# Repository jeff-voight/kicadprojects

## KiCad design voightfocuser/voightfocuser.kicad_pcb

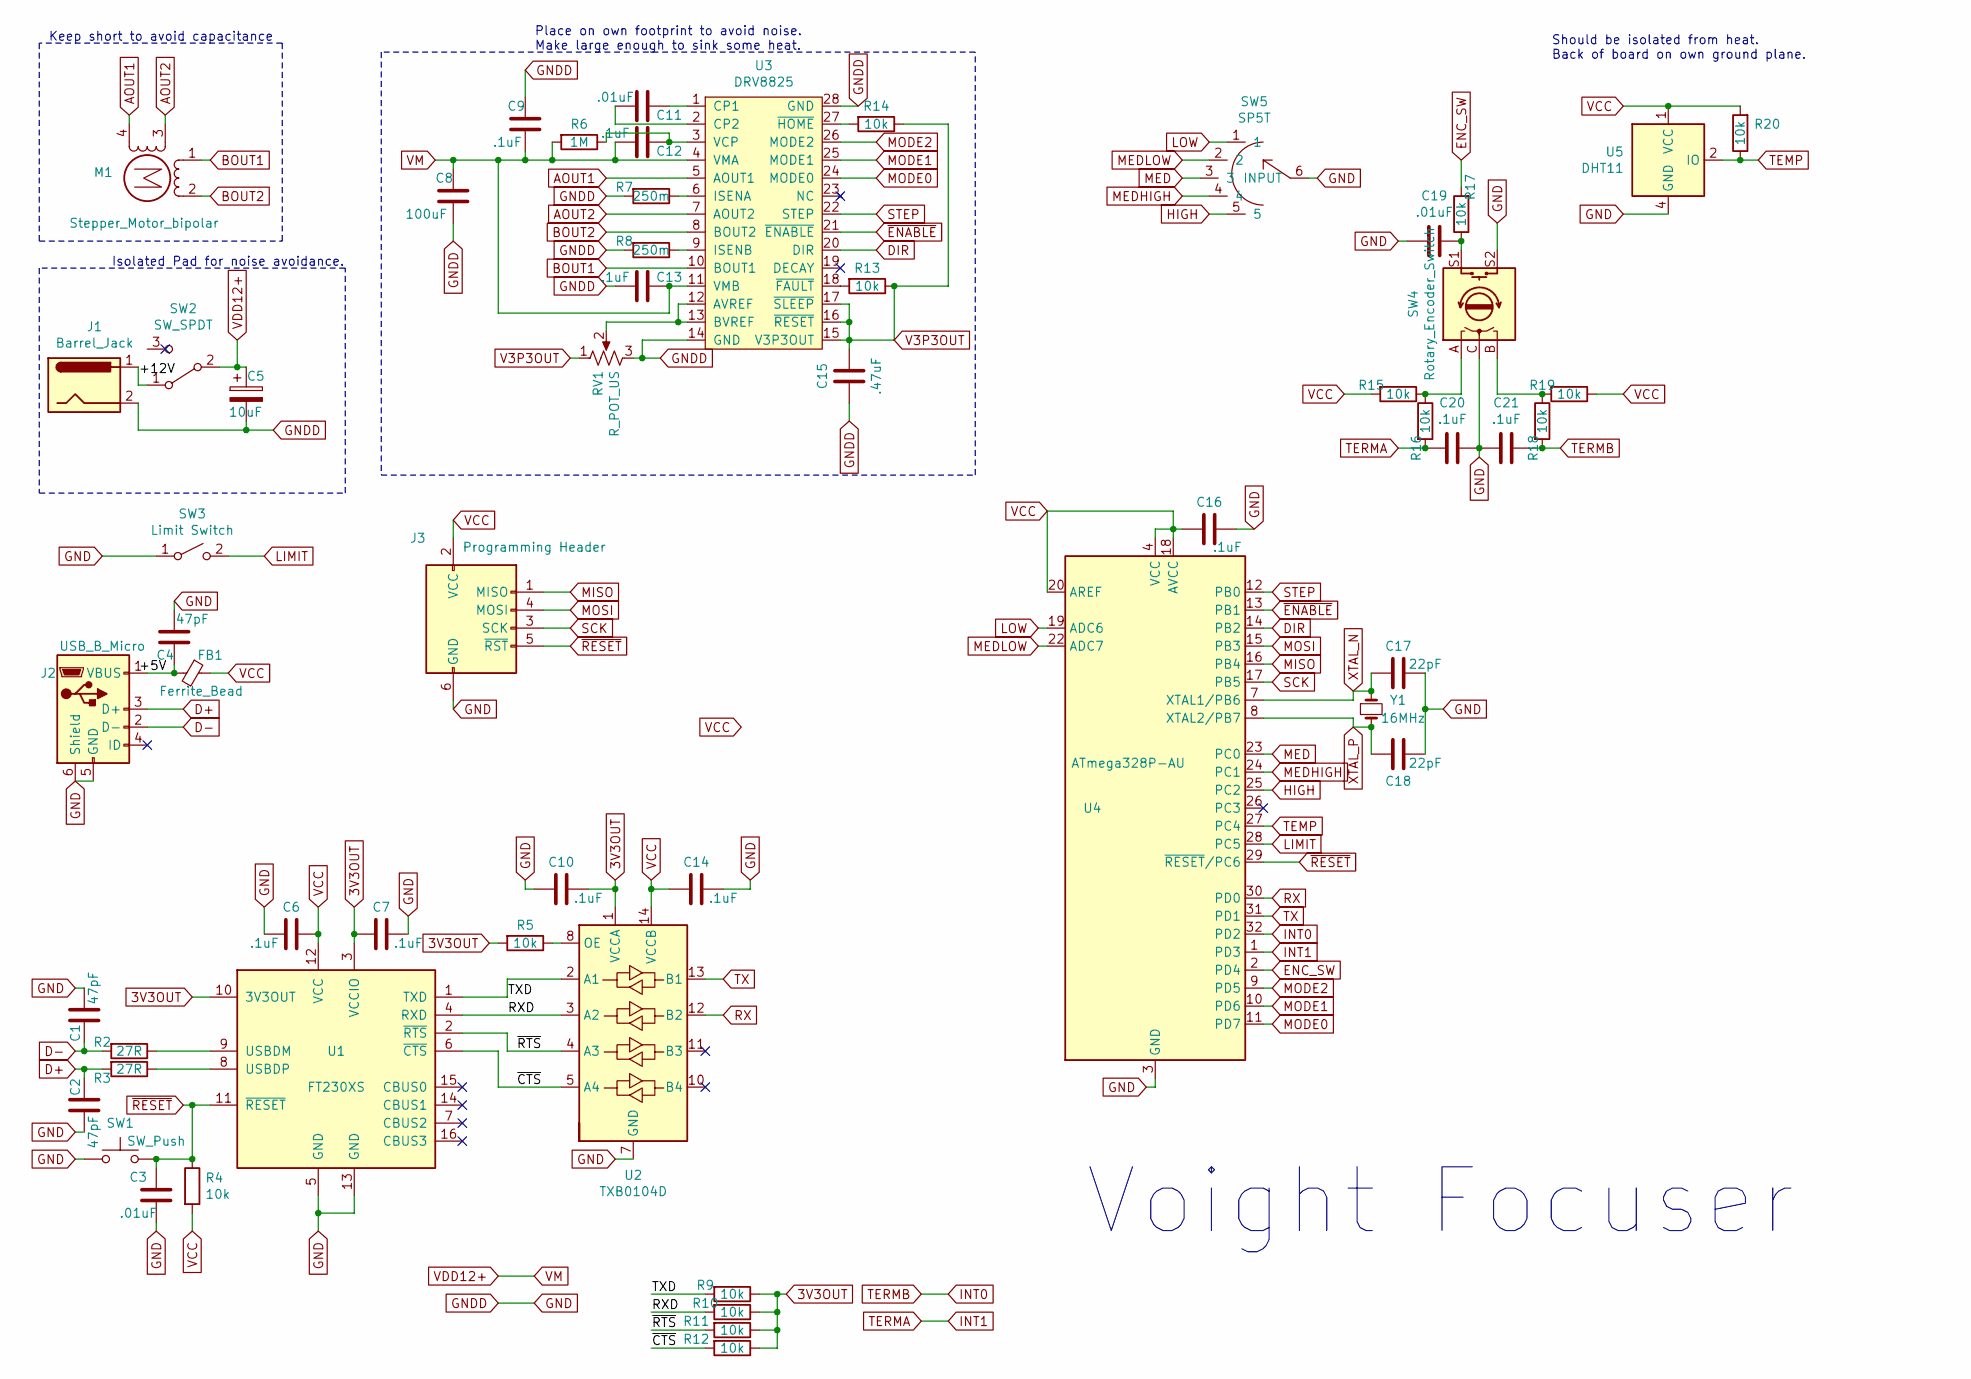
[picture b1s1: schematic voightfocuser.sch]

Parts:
C1, C2, C4: 47pF; C_0805_2012Metric_Pad1.15x1.40mm_HandSolder
C3, C11, C19: .01uF; C_0805_2012Metric_Pad1.15x1.40mm_HandSolder
C5: 10uF; C_0805_2012Metric_Pad1.15x1.40mm_HandSolder
C6, C7, C9, C10, C12, C13, C14, C16, C20, C21: .1uF; C_0805_2012Metric_Pad1.15x1.40mm_HandSolder
C8: 100uF; C_0805_2012Metric_Pad1.15x1.40mm_HandSolder
C15: .47uF; C_0805_2012Metric_Pad1.15x1.40mm_HandSolder
C17, C18: 22pF; C_0805_2012Metric_Pad1.15x1.40mm_HandSolder
FB1: Ferrite_Bead; LairdTech_28C0236-0JW-10
J1: Barrel_Jack; BarrelJack_CUI_PJ-063AH_Horizontal
J2: USB_B_Micro; USB_Micro-B_Amphenol_10103594-0001LF_Horizontal
J3: Programming Header; PinHeader_1x06_P2.54mm_Vertical
M1: Stepper_Motor_bipolar; PinHeader_1x04_P2.54mm_Vertical
R2, R3: 27R; R_0805_2012Metric_Pad1.15x1.40mm_HandSolder
R4, R5, R9, R10, R11, R12, R13, R14, R15, R16, R17, R18, R19, R20: 10k; R_0805_2012Metric_Pad1.15x1.40mm_HandSolder
R6: 1M; R_0805_2012Metric_Pad1.15x1.40mm_HandSolder
R7, R8: 250m; R_0805_2012Metric_Pad1.15x1.40mm_HandSolder
RV1: R_POT_US; Potentiometer_Bourns_TC33X_Vertical
SW1: SW_Push; PinHeader_1x02_P2.54mm_Vertical
SW2: SW_SPDT; SW_Slide_1P2T_CK_OS102011MS2Q
SW3: Limit Switch; PinHeader_1x02_P2.54mm_Vertical
SW4: Rotary_Encoder_Switch; RotaryEncoder_Alps_EC12E-Switch_Vertical_H20mm
SW5: SP5T; PinHeader_1x06_P2.54mm_Vertical
U1: FT230XS; SSOP-16_3.9x4.9mm_P0.635mm
U2: TXB0104D; SOIC-14_3.9x8.7mm_P1.27mm
U3: DRV8825; HTSSOP-28-1EP_4.4x9.7mm_P0.65mm_EP3.4x9.5mm_Mask2.4x6.17mm_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
U4: ATmega328P-AU; TQFP-32_7x7mm_P0.8mm
U5: DHT11; Aosong_DHT11_5.5x12.0_P2.54mm
Y1: 16MHz; Crystal_SMD_HC49-SD

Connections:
3V3OUT: C7.2, C10.1, R5.2, R9.1, R10.1, R11.1, R12.1, U1.3 (VCCIO), U1.10 (3V3OUT), U2.1 (VCCA)
/+12V: J1.1, SW2.1 (A)
/RXD: R10.2, U1.4 (RXD), U2.3 (A2)
/TXD: R9.2, U1.1 (TXD), U2.2 (A1)
/~CTS: R12.2, U1.6 (~CTS), U2.5 (A4)
/~RTS: R11.2, U1.2 (~RTS), U2.4 (A3)
AOUT1: M1.4, U3.5 (AOUT1)
AOUT2: M1.3, U3.7 (AOUT2)
BOUT1: M1.1, U3.10 (BOUT1)
BOUT2: M1.2 (-), U3.8 (BOUT2)
D+: C2.1, J2.3 (D+), R3.2
D-: C1.2, J2.2 (D-), R2.2
DIR: U3.20 (DIR), U4.14 (PB2)
ENC_SW: R17.2, U4.2 (PD4)
GND: C1.1, C2.2, C3.1, C4.1, C5.2, C6.2, C7.1, C8.2, C9.1, C10.2, C13.2, C14.1, C15.2, C16.1, C17.1, C18.1, C19.2, C20.1, C21.2, J1.2, J2.5 (GND), J2.6 (Shield), J3.6 (GND), R7.2, R8.2, RV1.3, SW1.1, SW3.1 (A), SW4.C, SW4.S2, SW5.6 (INPUT), U1.5 (GND), U1.13 (GND), U2.7 (GND), U3.14 (GND), U3.28 (GND), U4.3 (GND), U4.5 (GND), U4.21 (GND), U5.4 (GND)
HIGH: SW5.5, U4.25 (PC2)
INT0: C21.1, R18.2, U4.32 (PD2)
INT1: C20.2, R16.2, U4.1 (PD3)
LIMIT: SW3.2 (B), U4.28 (PC5)
LOW: SW5.1, U4.19 (ADC6)
MED: SW5.3, U4.23 (PC0)
MEDHIGH: SW5.4, U4.24 (PC1)
MEDLOW: SW5.2, U4.22 (ADC7)
MISO: J3.1 (MISO), U4.16 (PB4)
MODE0: U3.24 (MODE0), U4.11 (PD7)
MODE1: U3.25 (MODE1), U4.10 (PD6)
MODE2: U3.26 (MODE2), U4.9 (PD5)
MOSI: J3.4 (MOSI), U4.15 (PB3)
unnamed: C4.2, FB1.2, J2.1 (VBUS)
unnamed: C11.1, U3.1 (CP1)
unnamed: C11.2, U3.2 (CP2)
unnamed: C12.1, R6.1, U3.3 (VCP)
unnamed: C19.1, R17.1, SW4.S1
unnamed: R2.1, U1.9 (USBDM)
unnamed: R3.1, U1.8 (USBDP)
unnamed: R5.1, U2.8 (OE)
unnamed: R7.1, U3.6 (ISENA)
unnamed: R8.1, U3.9 (ISENB)
unnamed: R13.2, U3.18 (~FAULT)
unnamed: R14.2, U3.27 (~HOME)
unnamed: R15.1, R16.1, SW4.A
unnamed: R18.1, R19.2, SW4.B
unnamed: RV1.2, U3.12 (AVREF), U3.13 (BVREF)
RX: U2.12 (B2), U4.30 (PD0)
SCK: J3.3 (SCK), U4.17 (PB5)
STEP: U3.22 (STEP), U4.12 (PB0)
TEMP: R20.1, U4.27 (PC4), U5.2 (IO)
TX: U2.13 (B1), U4.31 (PD1)
V3P3OUT: C15.1, R13.1, R14.1, RV1.1, U3.15 (V3P3OUT), U3.16 (~RESET), U3.17 (~SLEEP)
VCC: C6.1, C14.2, C16.2, FB1.1, J3.2 (VCC), R4.2, R15.2, R19.1, R20.2, U1.12 (VCC), U2.14 (VCCB), U4.4 (VCC), U4.6 (VCC), U4.18 (AVCC), U4.20 (AREF), U5.1 (VCC)
VDD12+: C5.1, C8.1, C9.2, C12.2, C13.1, R6.2, SW2.2 (B), U3.4 (VMA), U3.11 (VMB)
XTAL_N: C17.2, U4.7 (XTAL1/PB6), Y1.1
XTAL_P: C18.2, U4.8 (XTAL2/PB7), Y1.2
~ENABLE: U3.21 (~ENABLE), U4.13 (PB1)
~RESET: C3.2, J3.5 (~RST), R4.1, SW1.2, U1.11 (~RESET), U4.29 (~RESET~/PC6)

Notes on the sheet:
Should be isolated from heat. Back of board on own ground plane.
Voight Focuser
Keep short to avoid capacitance
Place on own footprint to avoid noise. Make large enough to sink some heat.
Isolated Pad for noise avoidance.

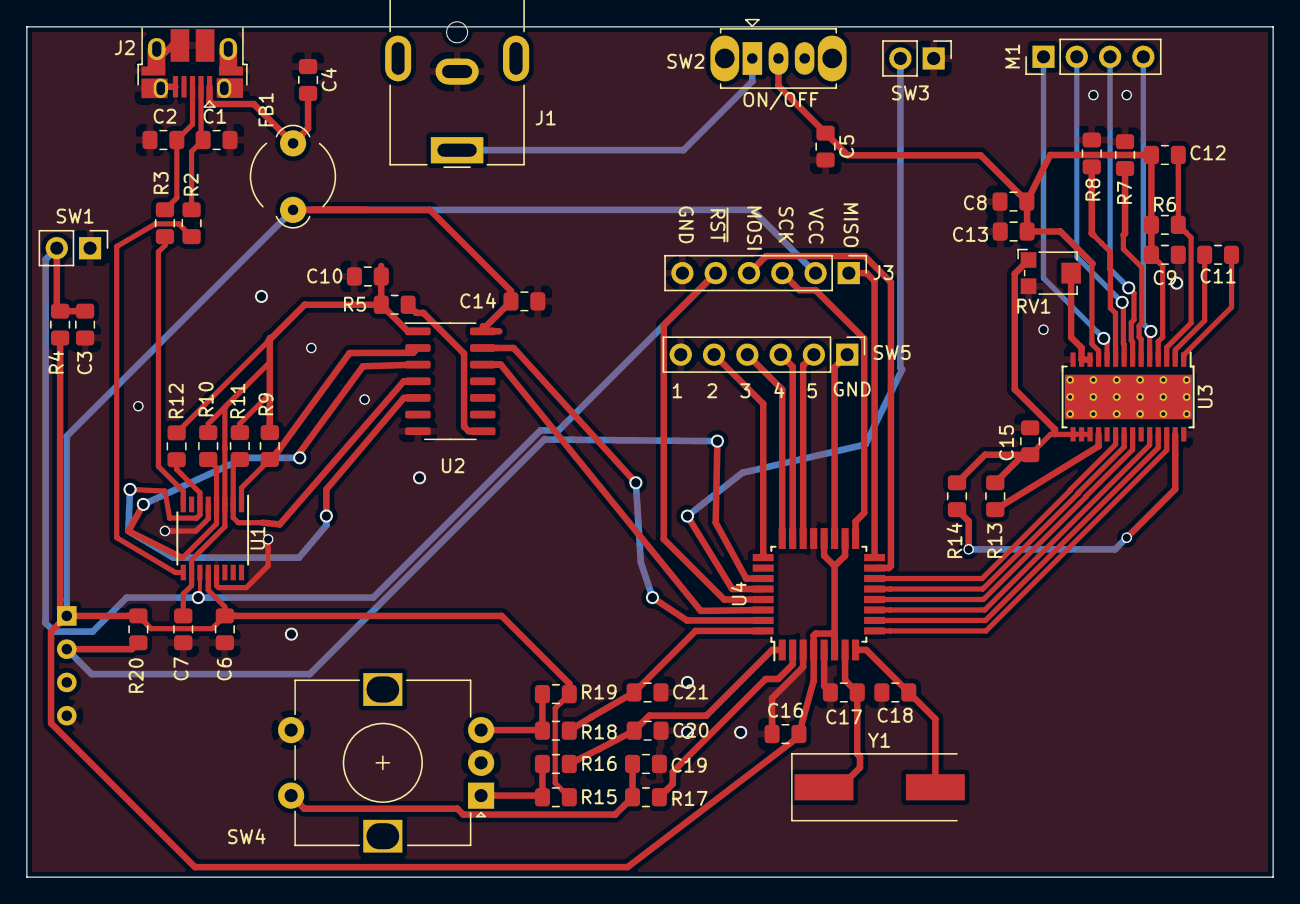
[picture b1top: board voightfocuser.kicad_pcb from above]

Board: 2 copper layers, 95.1 x 64.9 mm, 57 parts (1 on the bottom side), 55 nets.

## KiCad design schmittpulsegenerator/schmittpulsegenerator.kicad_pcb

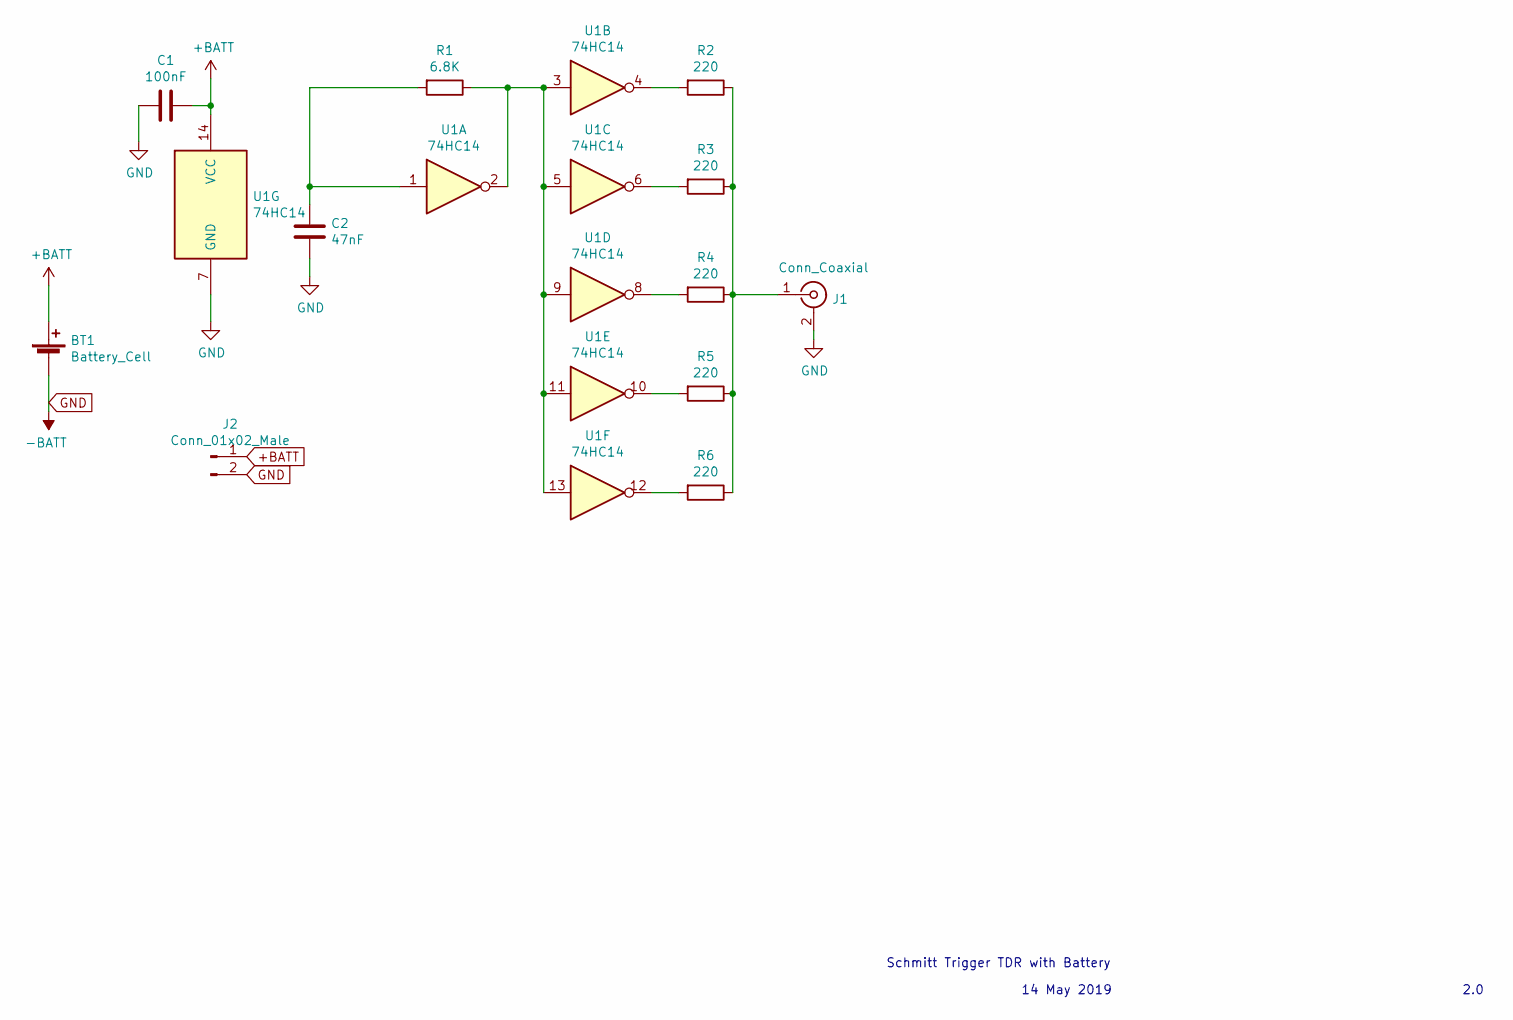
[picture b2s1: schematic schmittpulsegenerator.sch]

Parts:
BT1: Battery_Cell; BatteryHolder_Keystone_106_1x20mm
C1: 100nF; C_0603_1608Metric_Pad1.05x0.95mm_HandSolder
C2: 47nF; C_0603_1608Metric_Pad1.05x0.95mm_HandSolder
J1: Conn_Coaxial; BNC_PanelMountable_Vertical
J2: Conn_01x02_Male; PinHeader_1x02_P2.54mm_Vertical
R1: 6.8K; R_0603_1608Metric_Pad1.05x0.95mm_HandSolder
R2, R3, R4, R5, R6: 220; R_0603_1608Metric_Pad1.05x0.95mm_HandSolder
U1: 74HC14; SOIC-14_3.9x8.7mm_P1.27mm

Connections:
+BATT: BT1.1 (+), C1.1, J2.1, U1.14 (VCC)
GND: BT1.2 (-), C1.2, C2.2, J1.2 (Ext), J2.2, U1.7 (GND)
unnamed: C2.1, R1.2, U1.1
unnamed: J1.1 (In), R2.1, R3.1, R4.1, R5.1, R6.1
unnamed: R1.1, U1.2, U1.3, U1.5, U1.9, U1.11, U1.13
unnamed: R2.2, U1.4
unnamed: R3.2, U1.6
unnamed: R4.2, U1.8
unnamed: R5.2, U1.10
unnamed: R6.2, U1.12

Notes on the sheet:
Schmitt Trigger TDR with Battery
14 May 2019
2.0

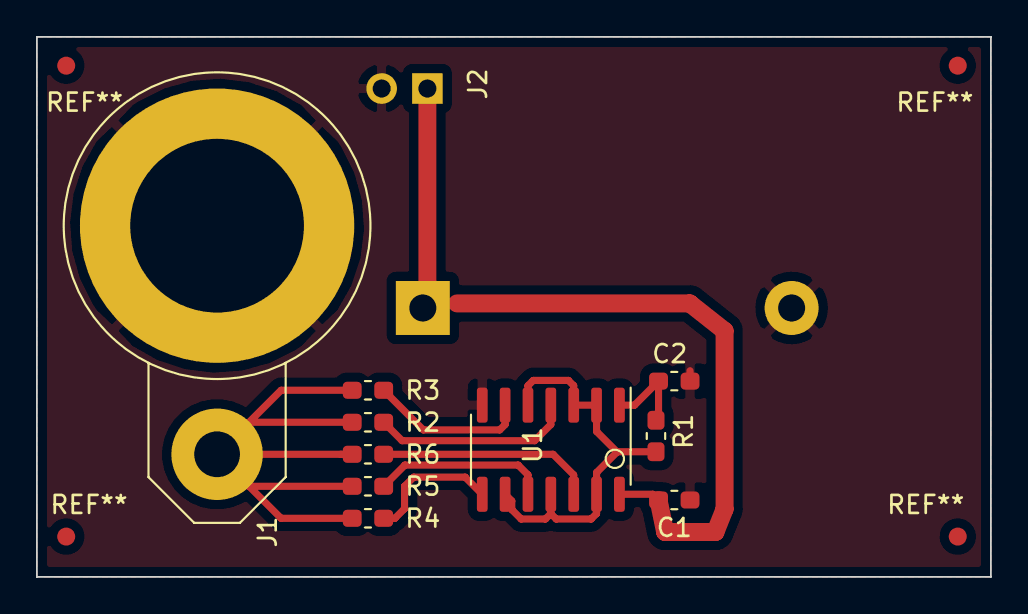
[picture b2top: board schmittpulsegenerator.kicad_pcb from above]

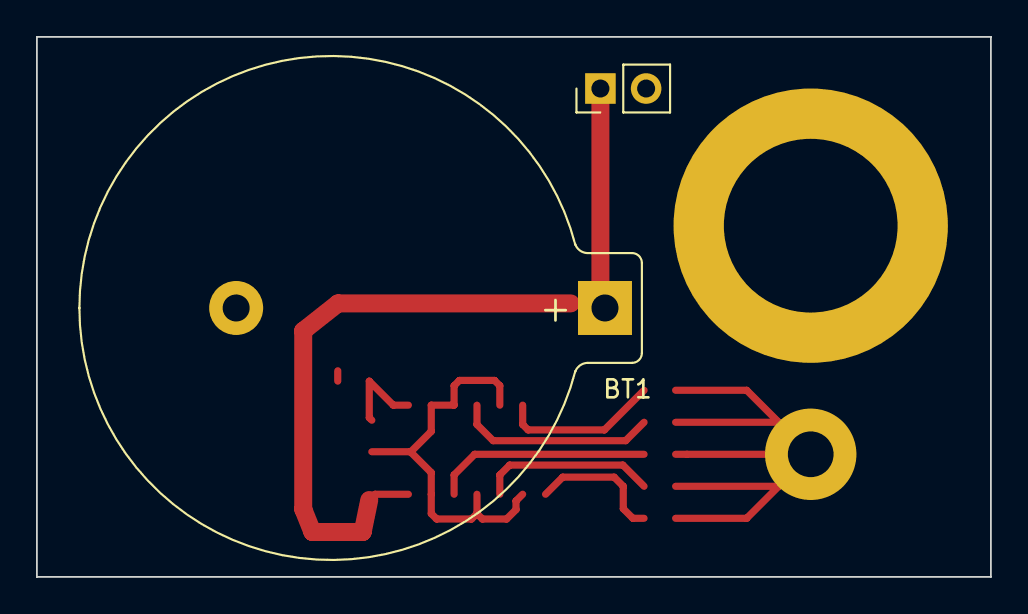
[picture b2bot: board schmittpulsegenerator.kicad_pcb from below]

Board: 2 copper layers, 53.0 x 30.0 mm, 12 parts (2 on the bottom side), 10 nets.

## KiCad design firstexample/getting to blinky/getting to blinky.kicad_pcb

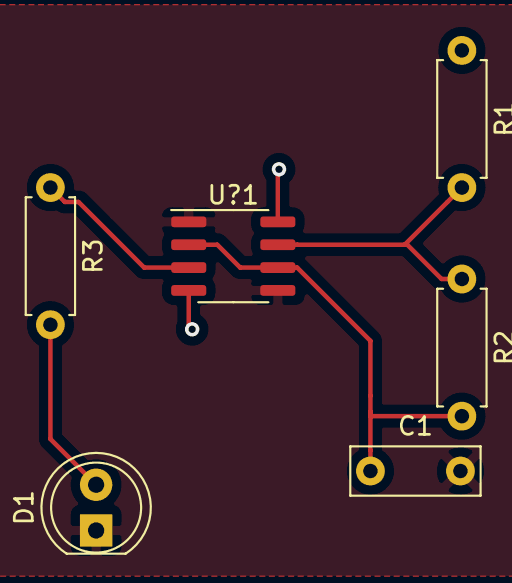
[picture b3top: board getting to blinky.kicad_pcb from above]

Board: 2 copper layers, 7 parts (1 on the bottom side), 6 nets.

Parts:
BT1: Battery_Cell; BatteryHolder_MPD_BC2003_1x2032
C1: 1uF; C_Disc_D7.0mm_W2.5mm_P5.00mm
D1: LED; LED_D5.0mm_FlatTop
R1, R3: 1K; R_Axial_DIN0207_L6.3mm_D2.5mm_P7.62mm_Horizontal
R2: 470K; R_Axial_DIN0207_L6.3mm_D2.5mm_P7.62mm_Horizontal
U?1: 7555; SOIC-8_3.9x4.9mm_P1.27mm

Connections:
/VDD: BT1.1, R1.1, U?1.4, U?1.8
GND: BT1.2, C1.2, D1.1, U?1.1, U?1.5
unnamed: C1.1, R2.2, U?1.2, U?1.6
unnamed: D1.2, R3.2
unnamed: R1.2, R2.1, U?1.7
unnamed: R3.1, U?1.3

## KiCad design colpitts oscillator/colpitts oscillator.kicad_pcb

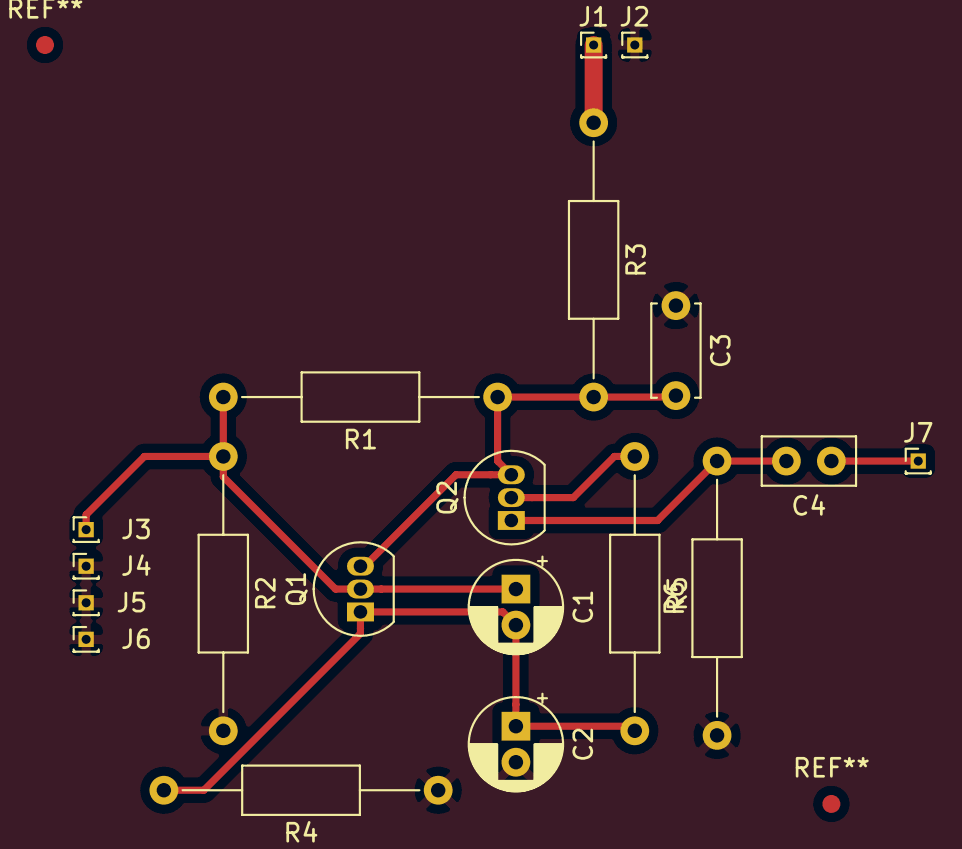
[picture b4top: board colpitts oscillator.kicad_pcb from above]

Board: 2 copper layers, 19 parts (0 on the bottom side), 8 nets.

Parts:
C1, C2: 470pF; CP_Radial_D5.0mm_P2.00mm
C3: 10nF; C_Disc_D5.0mm_W2.5mm_P5.00mm
C4: 10nF; C_Disc_D5.0mm_W2.5mm_P2.50mm
J1: 3-12V; PinHeader_1x01_P1.00mm_Vertical
J2: GND; PinHeader_1x01_P1.00mm_Vertical
J3: incrystal; PinHeader_1x01_P1.00mm_Vertical
J4: outcrystal1; PinHeader_1x01_P1.00mm_Vertical
J5: outcrystal2; PinHeader_1x01_P1.00mm_Vertical
J6: outcrystal3; PinHeader_1x01_P1.00mm_Vertical
J7: output; PinHeader_1x01_P1.00mm_Vertical
Q1, Q2: PN2222A; TO-92_Inline
R1, R2: 10k; R_Axial_DIN0207_L6.3mm_D2.5mm_P15.24mm_Horizontal
R3: 100; R_Axial_DIN0207_L6.3mm_D2.5mm_P15.24mm_Horizontal
R4, R5, R6: 1k; R_Axial_DIN0207_L6.3mm_D2.5mm_P15.24mm_Horizontal

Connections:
+12V: J1.1, R3.1
GND: C2.2, C3.1, J2.1, J4.1, J5.1, J6.1, R2.2, R4.1, R6.1
unnamed: C1.1, J3.1, Q1.2, R1.2, R2.1
unnamed: C1.2, C2.1, Q1.1, R4.2, R5.2
unnamed: C3.2, Q1.3, Q2.3, R1.1, R3.2
unnamed: C4.1, J7.1
unnamed: C4.2, Q2.1, R6.2
unnamed: Q2.2, R5.1

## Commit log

2019-05-14 Initial commit
    Just pulling in files on the drive.
2019-05-14 commit message
2019-05-14 started focuser
2019-05-15 stuff
2019-05-17 added parts
2019-05-18 datasheets
2019-05-22 adding resistors and caps to drv8825
2019-05-23 more components. switch 328p in
2019-05-24 new temperature
2019-05-25 changed encoders. Added caps.
2019-05-28 routing
2019-05-28 more route
2019-05-29 bigger board. routing prototype finished?
